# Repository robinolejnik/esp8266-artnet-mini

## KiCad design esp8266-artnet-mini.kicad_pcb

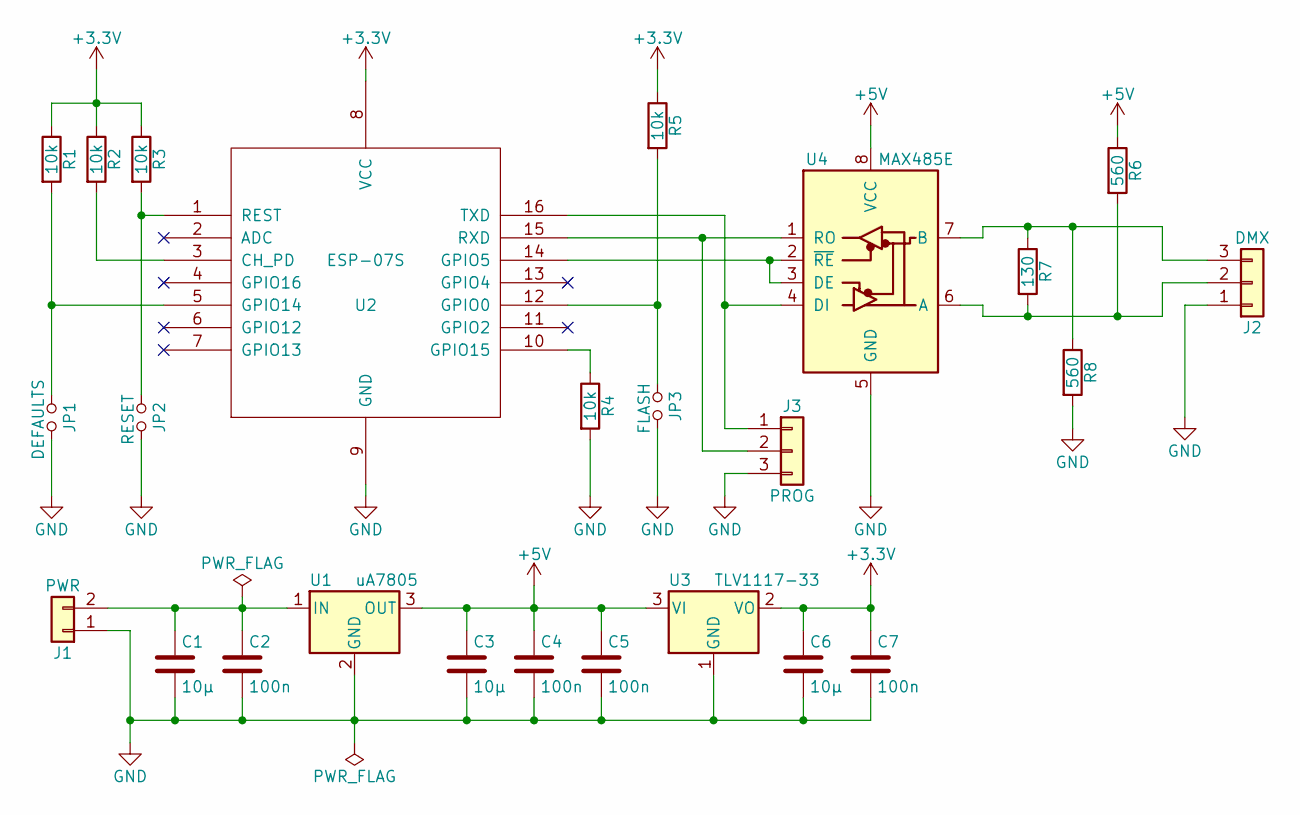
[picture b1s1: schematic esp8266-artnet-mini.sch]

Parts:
C1, C3, C6: 10µ; C_0805_HandSoldering
C2, C4, C5, C7: 100n; C_0805_HandSoldering
J1: PWR; TerminalBlock_bornier-2_P5.08mm
J2: DMX; TerminalBlock_bornier-3_P5.08mm
J3: PROG; Pin_Header_Straight_1x03_Pitch2.54mm
JP1: DEFAULTS; Pin_Header_Straight_1x02_Pitch2.00mm
JP2: RESET; Pin_Header_Straight_1x02_Pitch2.00mm
JP3: FLASH; Pin_Header_Straight_1x02_Pitch2.00mm
R1, R2, R3, R4, R5: 10k; R_0805_HandSoldering
R6, R8: 560; R_0805_HandSoldering
R7: 130; R_0805_HandSoldering
U1: uA7805; TO-220-3_Vertical
U2: ESP-07S
U3: TLV1117-33; SOT-223-3_TabPin2
U4: MAX485E; SOIC-8_3.9x4.9mm_Pitch1.27mm

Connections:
+3V3: C6.1, C7.1, R1.1, R2.1, R3.1, R5.1, U2.8 (VCC), U3.2 (VO)
+5V: C3.1, C4.1, C5.1, R6.1, U1.3 (OUT), U3.3 (VI), U4.8 (VCC)
GND: C1.2, C2.2, C3.2, C4.2, C5.2, C6.2, C7.2, J1.1, J2.1, J3.3, JP1.2, JP2.2, JP3.2, R4.2, R8.2, U1.2 (GND), U2.9 (GND), U3.1 (GND), U4.5 (GND)
unnamed: C1.1, C2.1, J1.2, U1.1 (IN)
unnamed: J2.2, R6.2, R7.2, U4.6 (A)
unnamed: J2.3, R7.1, R8.1, U4.7 (B)
unnamed: J3.1, U2.16 (TXD), U4.4 (DI)
unnamed: J3.2, U2.15 (RXD), U4.1 (RO)
unnamed: JP1.1, R1.2, U2.5 (GPIO14)
unnamed: JP2.1, R3.2, U2.1 (REST)
unnamed: JP3.1, R5.2, U2.12 (GPIO0)
unnamed: R2.2, U2.3 (CH_PD)
unnamed: R4.1, U2.10 (GPIO15)
unnamed: U2.14 (GPIO5), U4.2 (~RE), U4.3 (DE)

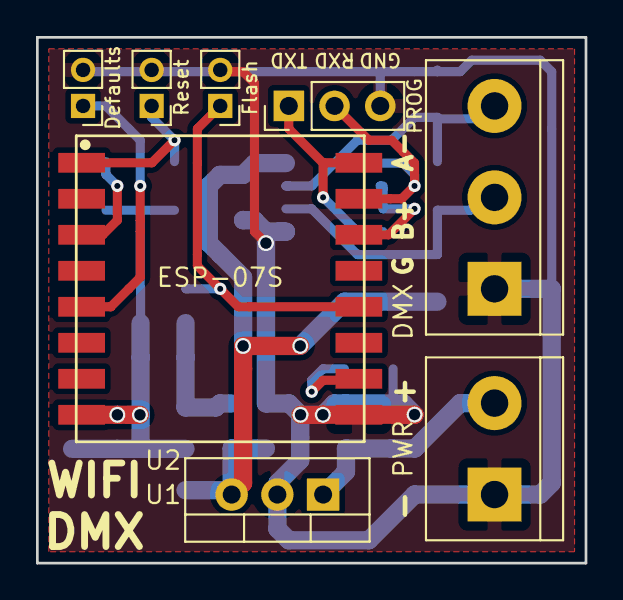
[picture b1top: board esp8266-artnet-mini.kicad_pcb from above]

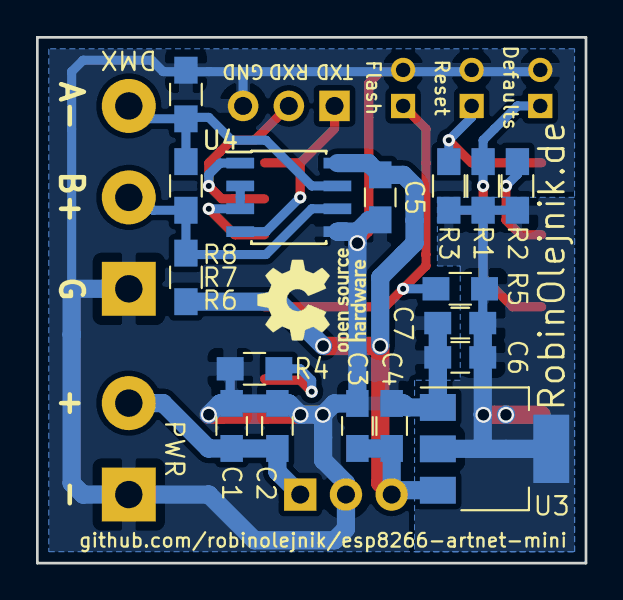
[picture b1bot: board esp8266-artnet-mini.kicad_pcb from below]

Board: 2 copper layers, 30.5 x 29.2 mm, 25 parts (17 on the bottom side), 14 nets.

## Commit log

2018-06-18 Added pcb files
2019-01-22 Updated project to KiCad 5
2019-01-22 updated silkscreen to match correct DMX polarity
